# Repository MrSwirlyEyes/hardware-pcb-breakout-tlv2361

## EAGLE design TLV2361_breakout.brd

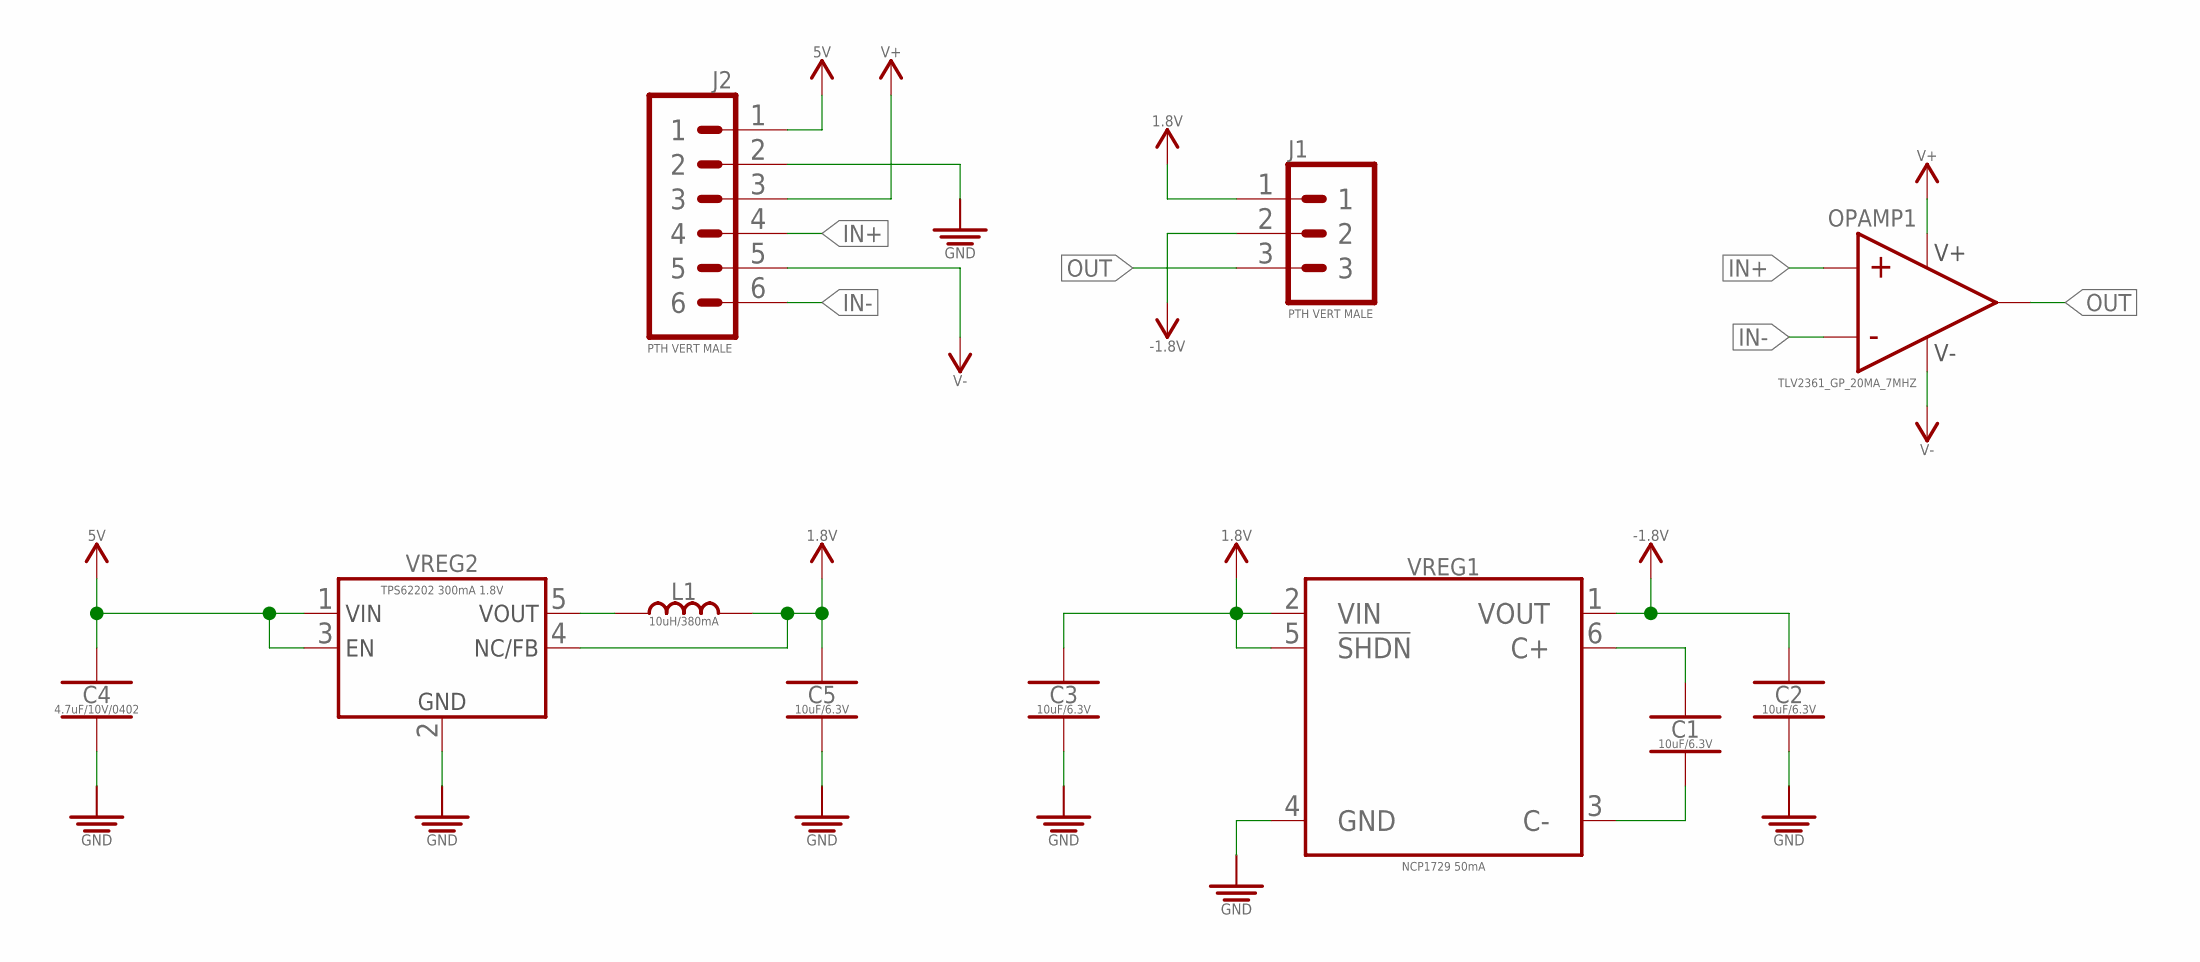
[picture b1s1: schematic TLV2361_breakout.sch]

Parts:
C1, C2, C3, C5: 10uF/6.3V; CAPC1005X55_SMD-0402
C4: 4.7uF/10V/0402; CAPC1005X55_SMD-0402
J1: PTH VERT MALE; HDRV3W64P254_1X3_762X254X838B
J2: PTH VERT MALE; HDRV6W64P254_1X6_1524X254X838B
L1: 10uH/380mA; INDC1608X60-0603
OPAMP1: TLV2361_GP_20MA_7MHZ; SOT95P280X145-5
VREG1: NCP1729 50mA; SOT95P275X100-6
VREG2: TPS62202 300mA 1.8V; SOT95P280X145-5

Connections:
1.8V: C3.1, C5.1, J1.1, L1.2, VREG1.2 (VIN), VREG1.5 (!SHDN), VREG2.4 (NC/FB)
5V: C4.1, J2.1, VREG2.1 (VIN), VREG2.3 (EN)
-1.8V: C2.1, J1.2, VREG1.1 (VOUT)
C+: C1.1, VREG1.6 (C+)
C-: C1.2, VREG1.3 (C-)
GND: C2.2, C3.2, C4.2, C5.2, J2.2, VREG1.4 (GND), VREG2.2 (GND)
IN+: J2.4, OPAMP1.1 (IN+)
IN-: J2.6, OPAMP1.3 (IN-)
unnamed: L1.1, VREG2.5 (VOUT)
OUT: J1.3, OPAMP1.4 (OUT)
V+: J2.3, OPAMP1.5 (V+)
V-: J2.5, OPAMP1.2 (V-)

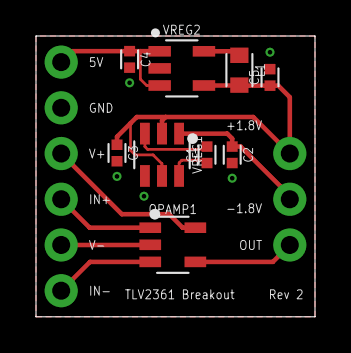
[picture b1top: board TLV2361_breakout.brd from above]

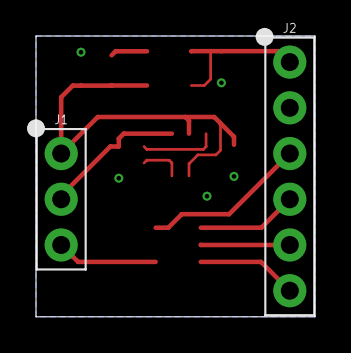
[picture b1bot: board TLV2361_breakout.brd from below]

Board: 2 copper layers, 15.5 x 15.6 mm, 11 parts (2 on the bottom side), 12 nets.

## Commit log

2019-09-28 Initialize repo.
